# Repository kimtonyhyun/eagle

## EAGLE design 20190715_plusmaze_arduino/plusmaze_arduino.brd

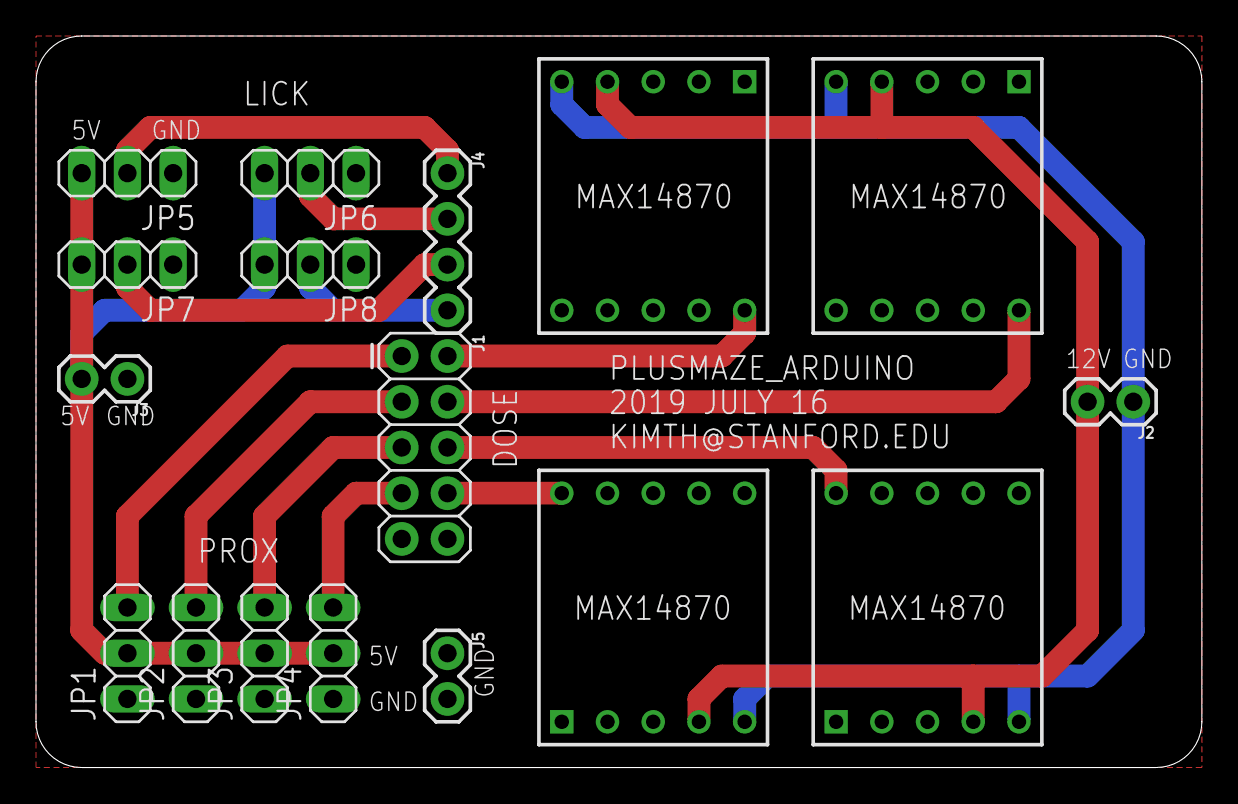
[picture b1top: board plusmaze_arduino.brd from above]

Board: 2 copper layers, 64.8 x 40.6 mm, 17 parts (0 on the bottom side), 16 nets.

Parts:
J1: 2X5
J2, J3, J5: 1X02
J4: 1X04
JP1, JP2, JP3, JP4, JP5, JP6, JP7, JP8: 1X03
U$1, U$2, U$3, U$4: POLOLU_MAX14870

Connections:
5V: J3.2, JP1.2, JP2.2, JP3.2, JP4.2, JP5.3, JP6.3, JP7.3, JP8.3
12V: J2.2, U$1.P$4, U$2.P$4, U$3.P$4, U$4.P$4
AGND: J2.1, U$1.P$5, U$2.P$5, U$3.P$5, U$4.P$5
DGND: J1.9, J1.10, J3.1, J5.1, J5.2, JP1.1, JP2.1, JP3.1, JP4.1, JP5.1, JP6.1, JP7.1, JP8.1, U$1.P$6, U$1.P$7, U$1.P$9, U$2.P$6, U$2.P$7, U$2.P$9, U$3.P$6, U$3.P$7, U$3.P$9, U$4.P$6, U$4.P$7, U$4.P$9
DOSE1: J1.2, U$1.P$10
DOSE2: J1.4, U$2.P$10
DOSE3: J1.6, U$3.P$10
DOSE4: J1.8, U$4.P$10
LICK1: J4.1, JP5.2
LICK2: J4.2, JP6.2
LICK3: J4.3, JP7.2
LICK4: J4.4, JP8.2
PROX1: J1.1, JP1.3
PROX2: J1.3, JP2.3
PROX3: J1.5, JP3.3
PROX4: J1.7, JP4.3

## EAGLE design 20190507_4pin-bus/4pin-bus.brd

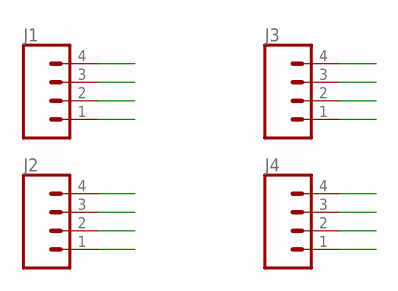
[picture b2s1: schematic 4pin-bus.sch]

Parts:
J1, J2, J3, J4: CONN_04; 1X04

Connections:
A: J1.1, J2.1, J3.1, J4.1
B: J1.2, J2.2, J3.2, J4.2
C: J1.3, J2.3, J3.3, J4.3
D: J1.4, J2.4, J3.4, J4.4

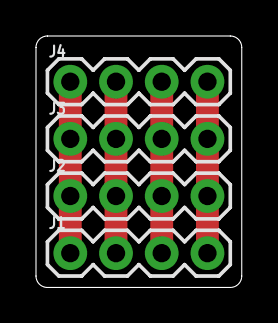
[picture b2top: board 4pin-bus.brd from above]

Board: 2 copper layers, 11.4 x 14.0 mm, 4 parts (0 on the bottom side), 4 nets.

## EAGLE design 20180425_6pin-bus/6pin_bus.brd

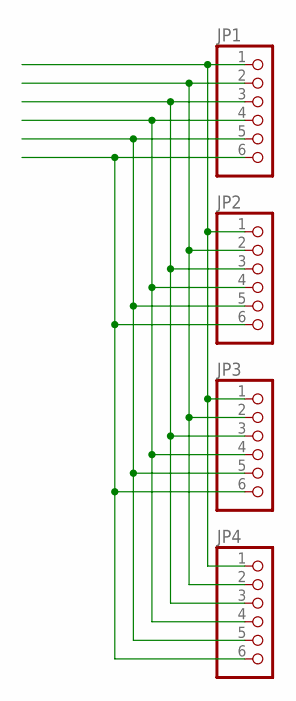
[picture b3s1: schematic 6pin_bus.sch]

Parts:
JP1, JP2, JP3, JP4: PINHD-1X6; 1X06

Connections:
unnamed: JP1.1, JP2.1, JP3.1, JP4.1
unnamed: JP1.2, JP2.2, JP3.2, JP4.2
unnamed: JP1.3, JP2.3, JP3.3, JP4.3
unnamed: JP1.4, JP2.4, JP3.4, JP4.4
unnamed: JP1.5, JP2.5, JP3.5, JP4.5
unnamed: JP1.6, JP2.6, JP3.6, JP4.6

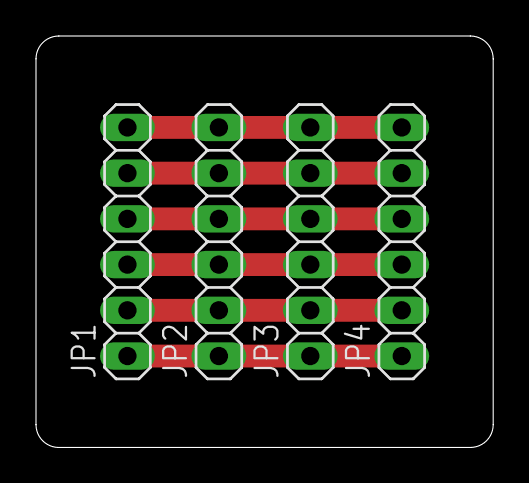
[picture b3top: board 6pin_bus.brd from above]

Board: 2 copper layers, 25.4 x 22.9 mm, 4 parts (0 on the bottom side), 6 nets.

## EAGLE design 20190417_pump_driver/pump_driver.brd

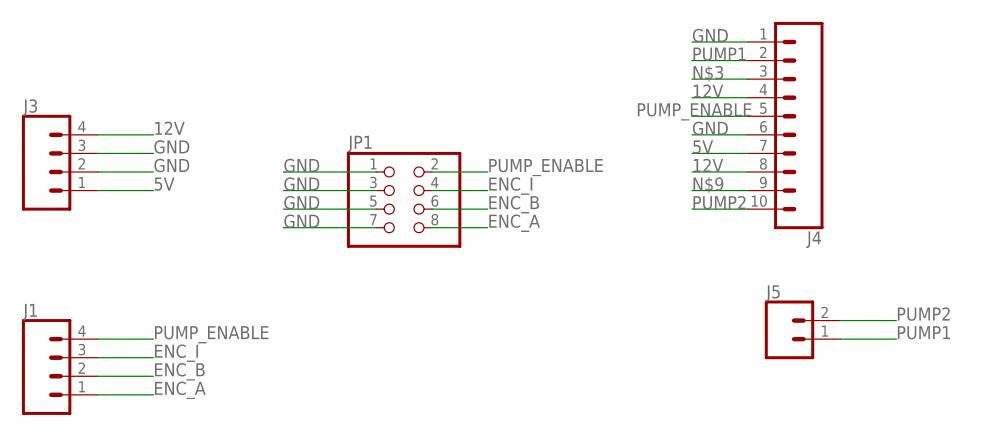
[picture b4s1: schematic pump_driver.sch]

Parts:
J1, J3: CONN_04; 1X04
J4: CONN_10"; 1X10
J5: CONN_02; 1X02
JP1: PINHD-2X4; 2X04

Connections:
5V: J3.1, J4.7
12V: J3.4, J4.4, J4.8
ENC_A: J1.1, JP1.8
ENC_B: J1.2, JP1.6
ENC_I: J1.3, JP1.4
GND: J3.2, J3.3, J4.1, J4.6, JP1.1, JP1.3, JP1.5, JP1.7
PUMP1: J4.2, J5.1
PUMP2: J4.10, J5.2
PUMP_ENABLE: J1.4, J4.5, JP1.2

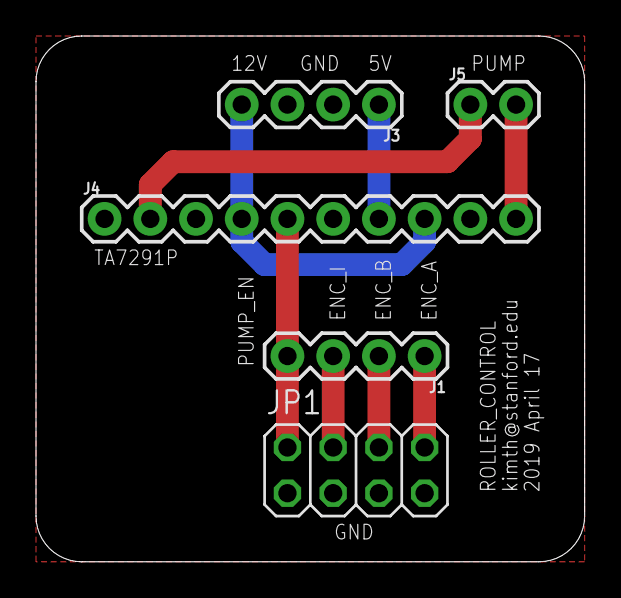
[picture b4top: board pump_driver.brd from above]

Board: 2 copper layers, 30.5 x 29.2 mm, 5 parts (0 on the bottom side), 9 nets.

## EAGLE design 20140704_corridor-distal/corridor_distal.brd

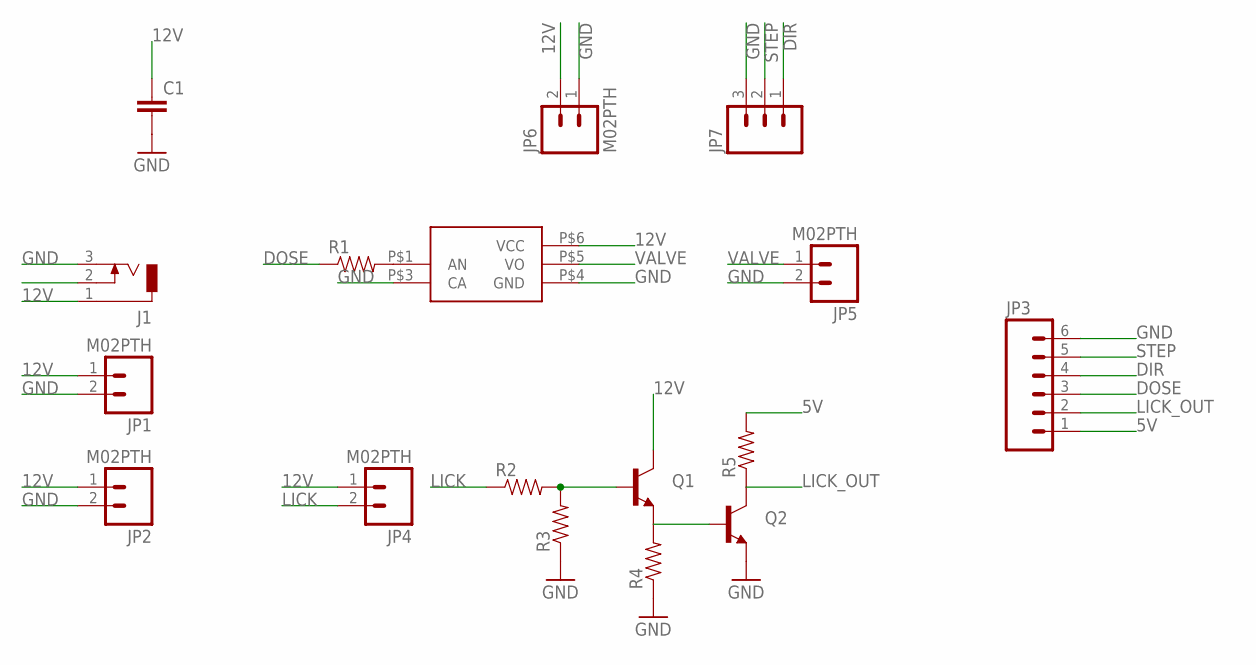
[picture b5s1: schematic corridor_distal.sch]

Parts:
C1: CAP1206; 1206
J1: DCJ0303
JP1, JP2, JP4, JP5, JP6: M02PTH; 1X02
JP3: M06SIP; 1X06
JP7: M03PTH; 1X03
Q1, Q2: TRANSISTOR_NPNTO92; TO-92
R1, R2, R3, R4, R5: RESISTOR1206; 1206
U$1: TLP701

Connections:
5V: JP3.1, R5.2
12V: C1.1, J1.1, JP1.1, JP2.1, JP4.1, JP6.2, Q1.3 (C), U$1.P$6 (VCC)
DIR: JP3.4, JP7.1
DOSE: JP3.3, R1.1
GND: C1.2, J1.3, JP1.2, JP2.2, JP3.6, JP5.2, JP6.1, JP7.3, Q2.1 (E), R3.1, R4.1, U$1.P$3 (CA), U$1.P$4 (GND)
LICK: JP4.2, R2.1
LICK_OUT: JP3.2, Q2.3 (C), R5.1
unnamed: R1.2, U$1.P$1 (AN)
unnamed: Q1.2 (B), R2.2, R3.2
unnamed: Q1.1 (E), Q2.2 (B), R4.2
STEP: JP3.5, JP7.2
VALVE: JP5.1, U$1.P$5 (VO)

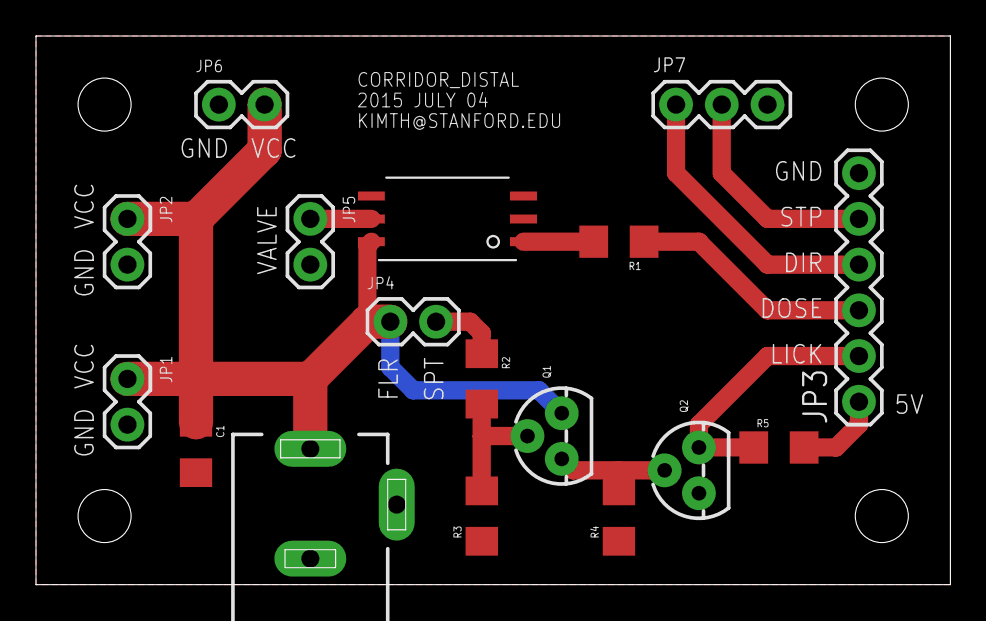
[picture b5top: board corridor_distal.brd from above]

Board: 2 copper layers, 50.8 x 30.5 mm, 17 parts (0 on the bottom side), 12 nets.

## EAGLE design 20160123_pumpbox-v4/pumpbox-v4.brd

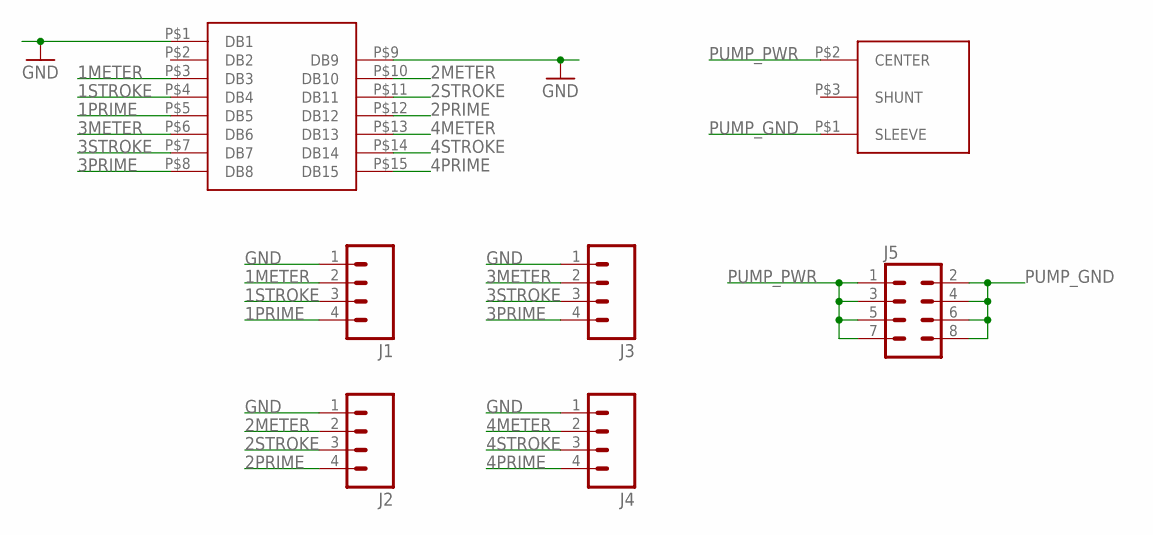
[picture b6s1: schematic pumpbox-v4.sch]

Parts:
J1, J2, J3, J4: M04PTH; 1X04
J5: M04X2; 2X4
U$1: DB15
U$2: RAPC10P

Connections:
1METER: J1.2, U$1.P$3 (DB3)
1PRIME: J1.4, U$1.P$5 (DB5)
1STROKE: J1.3, U$1.P$4 (DB4)
2METER: J2.2, U$1.P$10 (DB10)
2PRIME: J2.4, U$1.P$12 (DB12)
2STROKE: J2.3, U$1.P$11 (DB11)
3METER: J3.2, U$1.P$6 (DB6)
3PRIME: J3.4, U$1.P$8 (DB8)
3STROKE: J3.3, U$1.P$7 (DB7)
4METER: J4.2, U$1.P$13 (DB13)
4PRIME: J4.4, U$1.P$15 (DB15)
4STROKE: J4.3, U$1.P$14 (DB14)
GND: J1.1, J2.1, J3.1, J4.1, U$1.P$1 (DB1), U$1.P$9 (DB9)
PUMP_GND: J5.2, J5.4, J5.6, J5.8, U$2.P$1 (SLEEVE)
PUMP_PWR: J5.1, J5.3, J5.5, J5.7, U$2.P$2 (CENTER)

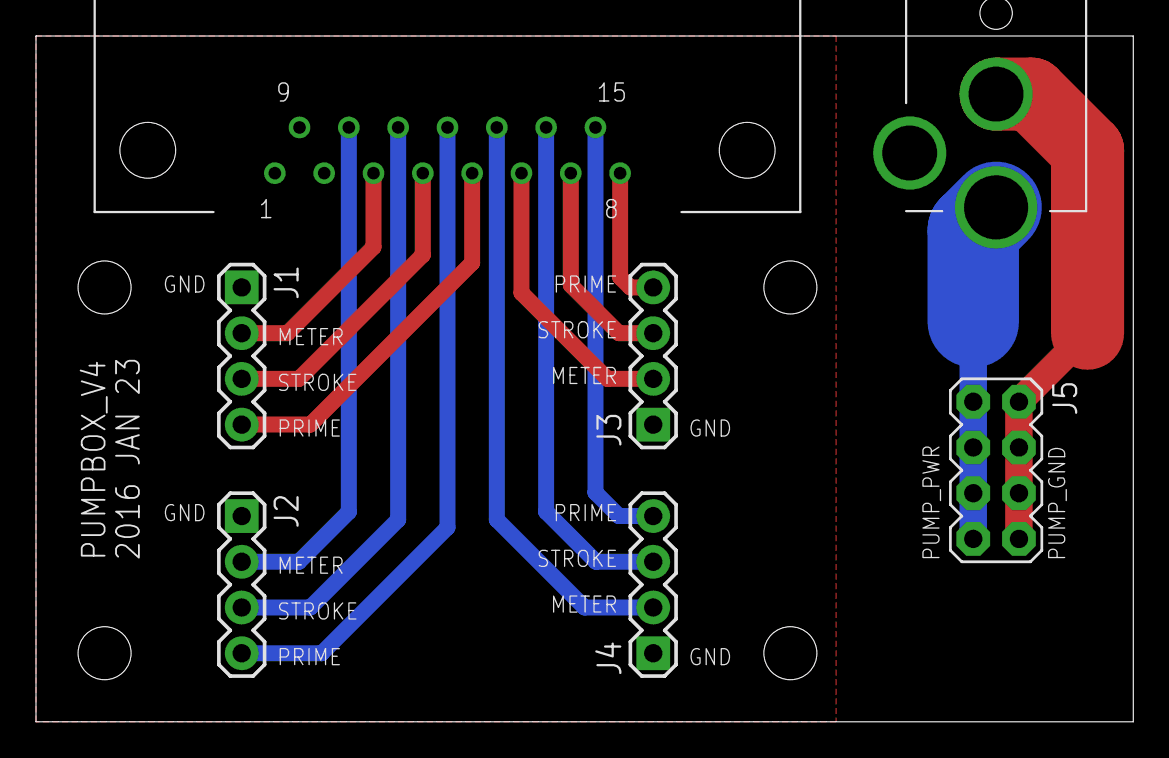
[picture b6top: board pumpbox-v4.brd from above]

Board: 2 copper layers, 61.0 x 38.1 mm, 7 parts (0 on the bottom side), 15 nets.

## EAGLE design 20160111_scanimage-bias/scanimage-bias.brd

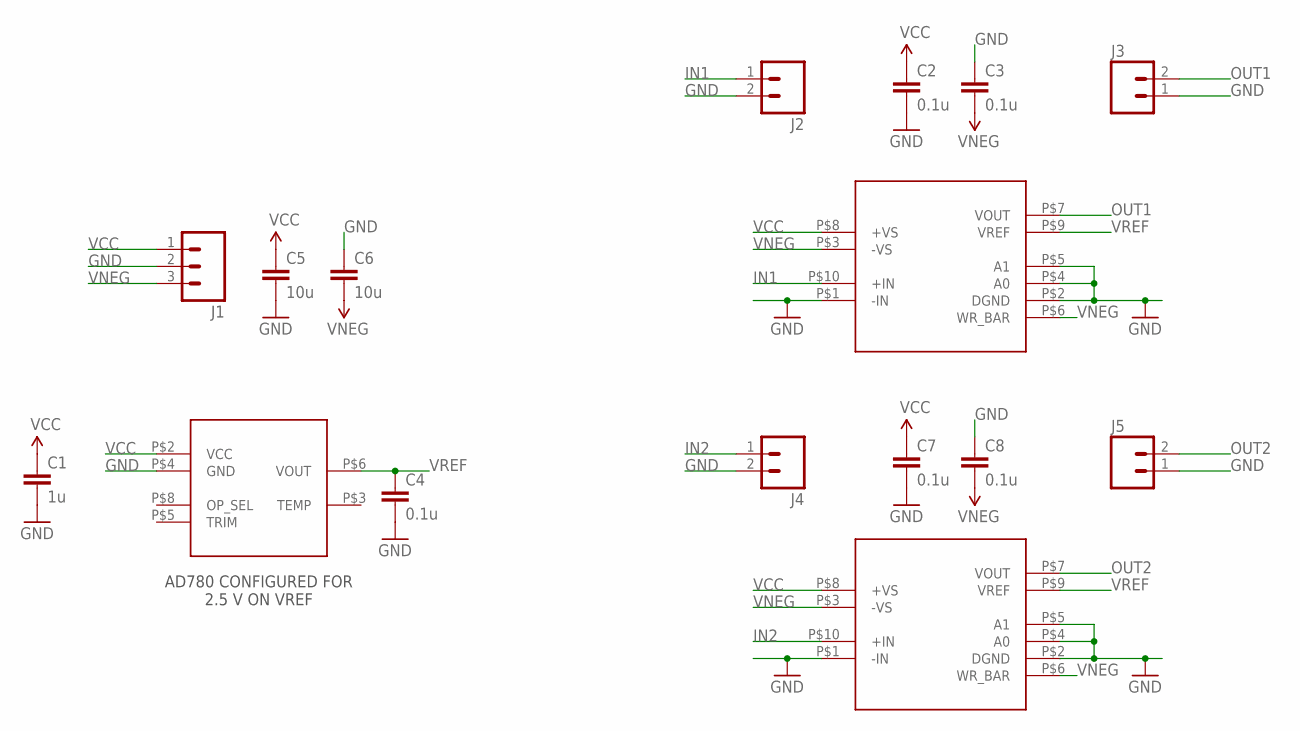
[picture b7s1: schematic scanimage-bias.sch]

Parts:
C1: 1u; 1206
C2, C3, C4, C7, C8: 0.1u; 1206
C5, C6: 10u; 1206
J1: M03PTH; 1X03
J2, J3, J4, J5: M02PTH; 1X02
U$1: AD780; SOIC-8
U$2, U$3: AD8250; MSOP-10

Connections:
GND: C1.2, C2.2, C3.1, C4.2, C5.2, C6.1, C7.2, C8.1, J1.2, J2.2, J3.1, J4.2, J5.1, U$1.P$4 (GND), U$2.P$1 (-IN), U$2.P$2 (DGND), U$2.P$4 (A0), U$2.P$5 (A1), U$3.P$1 (-IN), U$3.P$2 (DGND), U$3.P$4 (A0), U$3.P$5 (A1)
IN1: J2.1, U$2.P$10 (+IN)
IN2: J4.1, U$3.P$10 (+IN)
OUT1: J3.2, U$2.P$7 (VOUT)
OUT2: J5.2, U$3.P$7 (VOUT)
VCC: C1.1, C2.1, C5.1, C7.1, J1.1, U$1.P$2 (VCC), U$2.P$8 (+VS), U$3.P$8 (+VS)
VNEG: C3.2, C6.2, C8.2, J1.3, U$2.P$3 (-VS), U$2.P$6 (WR_BAR), U$3.P$3 (-VS), U$3.P$6 (WR_BAR)
VREF: C4.1, U$1.P$6 (VOUT), U$2.P$9 (VREF), U$3.P$9 (VREF)

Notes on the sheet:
AD780 CONFIGURED FOR 2.5 V ON VREF

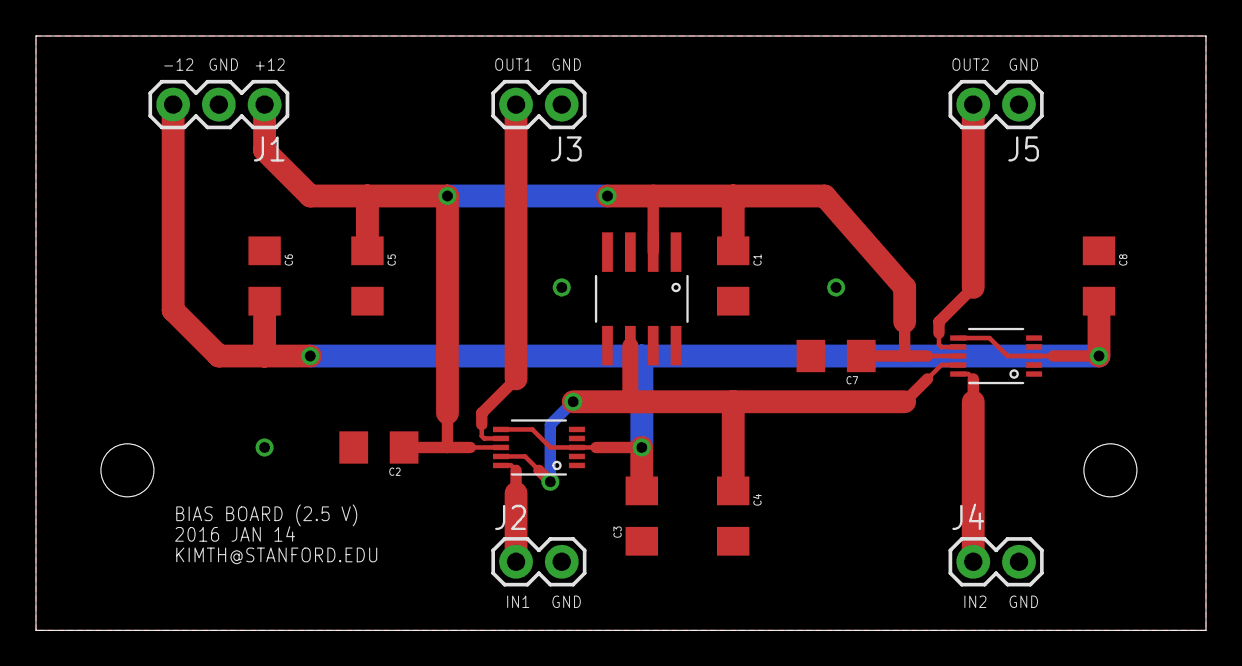
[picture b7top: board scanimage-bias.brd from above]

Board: 2 copper layers, 65.0 x 33.0 mm, 16 parts (0 on the bottom side), 8 nets.

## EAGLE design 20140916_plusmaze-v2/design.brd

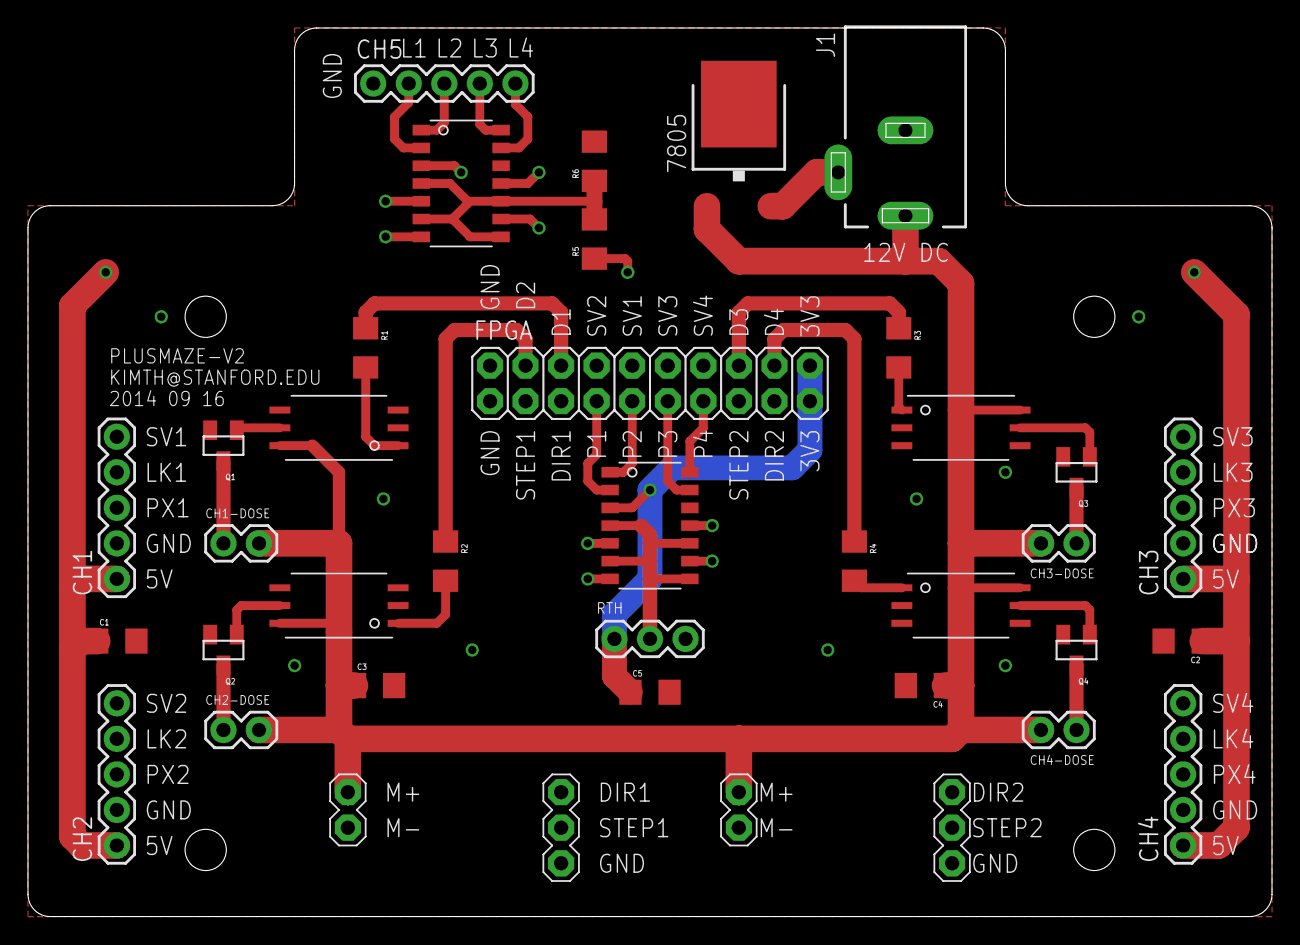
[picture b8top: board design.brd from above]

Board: 4 copper layers, 88.9 x 63.5 mm, 36 parts (0 on the bottom side), 46 nets.

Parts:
7805: 7805DT; TO252
C1, C2, C3, C4, C5: 1206
CH1, CH2, CH3, CH4, CH5: 1X05
CH1-DOSE, CH2-DOSE, CH3-DOSE, CH4-DOSE: M02PTH; 1X02
FPGA: 2X10
J1: DCJ0303
Q1, Q2, Q3, Q4: MOSFET-NCHANNELBSS123LT1G; SOT23
R1, R2, R3, R4, R5, R6: 1206
RTH: 1X03
U$1, U$2, U$3, U$4: TLP701
U$5, U$8: BA10339; BA10339-SOP14
U$6, U$7: EASYDRIVER

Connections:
3.3V: C5.1, FPGA.19, FPGA.20, RTH.1, U$5.P$3
5V: 7805.2, C1.1, C2.1, CH1.1, CH2.1, CH3.1, CH4.1, J1.2, R5.1, U$8.P$3
12V: 7805.1, C3.1, C4.1, CH1-DOSE.2, CH2-DOSE.2, CH3-DOSE.2, CH4-DOSE.2, J1.1, U$1.P$6, U$2.P$6, U$3.P$6, U$4.P$6, U$6.P$1, U$7.P$1
D1: FPGA.6, R1.1
D1_DRAIN: CH1-DOSE.1, Q1.3
D2: FPGA.4, R2.1
D2_DRAIN: CH2-DOSE.1, Q2.3
D3: FPGA.16, R3.1
D3_DRAIN: CH3-DOSE.1, Q3.3
D4: FPGA.18, R4.1
D4_DRAIN: CH4-DOSE.1, Q4.3
DIR1: FPGA.5, U$6.P$3
DIR2: FPGA.17, U$7.P$3
GND: 7805.3, C1.2, C2.2, C3.2, C4.2, C5.2, CH1.2, CH2.2, CH3.2, CH4.2, CH5.1, FPGA.1, FPGA.2, J1.3, Q1.2, Q2.2, Q3.2, Q4.2, R6.2, RTH.3, U$1.P$3, U$1.P$4, U$2.P$3, U$2.P$4, U$3.P$3, U$3.P$4, U$4.P$3, U$4.P$4, U$5.P$12, U$6.P$2, U$6.P$5, U$7.P$2, U$7.P$5, U$8.P$12
L1: CH5.2, U$8.P$2
L2: CH5.3, U$8.P$1
L3: CH5.4, U$8.P$14
L4: CH5.5, U$8.P$13
LICK1: CH1.4, U$8.P$5
LICK2: CH2.4, U$8.P$7
LICK3: CH3.4, U$8.P$11
LICK4: CH4.4, U$8.P$9
unnamed: Q1.1, U$1.P$5
unnamed: Q2.1, U$2.P$5
unnamed: Q3.1, U$3.P$5
unnamed: Q4.1, U$4.P$5
unnamed: R1.2, U$1.P$1
unnamed: R2.2, U$2.P$1
unnamed: R3.2, U$3.P$1
unnamed: R4.2, U$4.P$1
P1: FPGA.7, U$5.P$2
P2: FPGA.9, U$5.P$1
P3: FPGA.11, U$5.P$13
P4: FPGA.13, U$5.P$14
PROX1: CH1.3, U$5.P$5
PROX2: CH2.3, U$5.P$7
PROX3: CH3.3, U$5.P$11
PROX4: CH4.3, U$5.P$9
SERVO1: CH1.5, FPGA.10
SERVO2: CH2.5, FPGA.8
SERVO3: CH3.5, FPGA.12
SERVO4: CH4.5, FPGA.14
STEP1: FPGA.3, U$6.P$4
STEP2: FPGA.15, U$7.P$4
VTH: RTH.2, U$5.P$4, U$5.P$6, U$5.P$8, U$5.P$10
VTH2: R5.2, R6.1, U$8.P$4, U$8.P$6, U$8.P$8, U$8.P$10

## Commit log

2016-01-11 Bias circuit for ScanImage
2016-01-12 No lock files
2016-01-12 Stop tracking lock files
2016-01-14 Made libraries
2016-01-14 Finish schematic
2016-01-14 ScanImage board WIP
2016-01-14 Completed board -- rev1
2016-01-23 Remove autobackups
2016-01-23 Pumpbox_v4 redrawn
2016-01-23 Retract the DB15 header
2018-04-25 Some old designs...
2018-04-25 6-pin bus
2019-04-18 First update in a while!
2019-07-16 Pololu motor
2019-07-16 Plusmaze arduino
2019-07-16 Plusmaze Arduino add lickometers

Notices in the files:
parts and their libraries:
SparkFun-Connectors: Licensing: CC v3.0 Share-Alike You are welcome to use this library for commercial purposes.
SparkFun-Capacitors: Licensing: Creative Commons ShareAlike 4.0 International - https://creativecommons.org/licenses/by-sa/4.0
